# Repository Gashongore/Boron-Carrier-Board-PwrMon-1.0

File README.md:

# Boron-Carrier-Board-PwrWon-1.0
1. modified Particle Boron-Carrier-Board for Power Monitoring
2. It is using all analog pins

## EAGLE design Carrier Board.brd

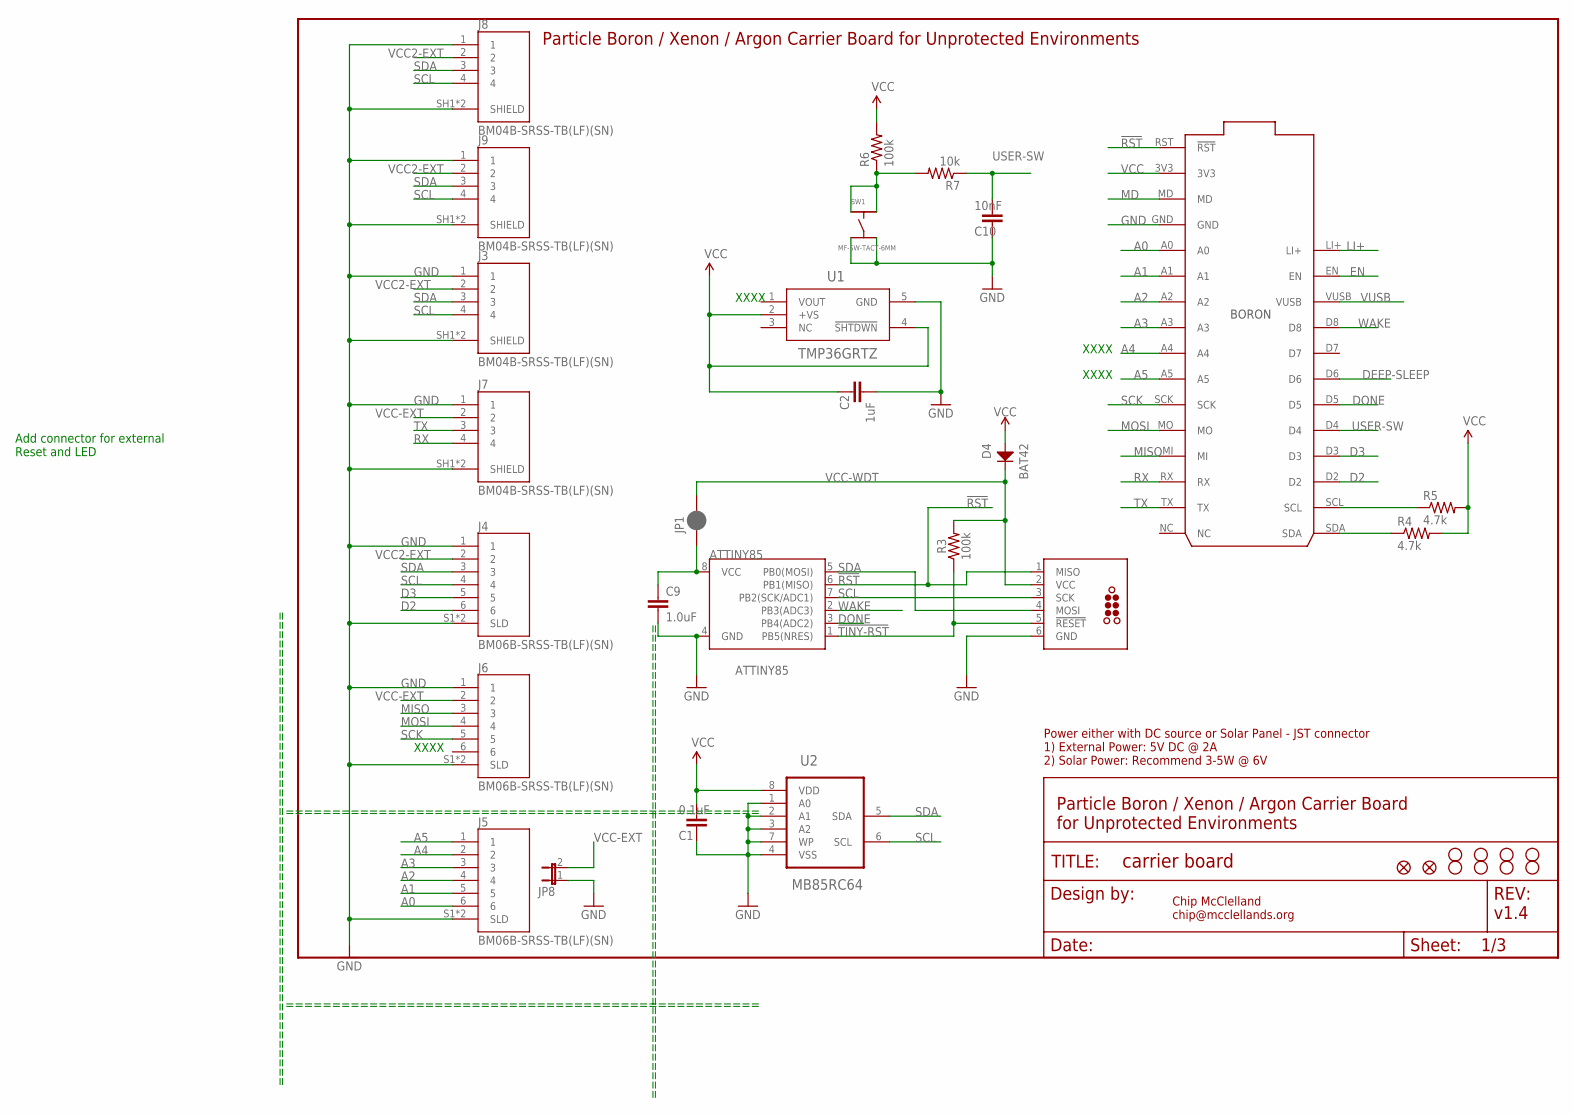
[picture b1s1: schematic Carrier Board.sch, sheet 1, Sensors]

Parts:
ATTINY85: ATTINY85; SO08-EIAJ; MPN ATTINY85-20SUR
C1: 0.1uF; 0805@1; MPN MF-CAP-0805-0.1uF
C2: 1uF; 0805@1; MPN MF-CAP-0805-1uF
C9: 1.0uF; 0805; MPN MF-CAP-0805-0.1uF
C10: 10nF; 0805@1; MPN 08051C103K4T2A
D4: BAT42; SOD-123
FD1, FD2: FIDUCIALUFIDUCIAL; FIDUCIAL-MICRO
FRAME1: FRAME-LETTER; CREATIVE_COMMONS
H1, H2, H3, H4: STAND-OFF-M2.5
ICSP: TCP2030-MCP-NL; TC2030-MCP-NL
J3, J7, J8, J9: BM04B-SRSS-TB(LF)(SN); CONN_BM04B-SRSS-TBT(LF)(SN)
J4, J5, J6: BM06B-SRSS-TB(LF)(SN); JST_BM06B-SRSS-TB(LF)(SN)
JP1: JUMPER-SMT_2_NC_PASTE_SILK; SMT-JUMPER_2_NC_PASTE_SILK
JP3, JP4, JP5, JP6: STAND-OFF
JP8: JP1E; JP1
P1: Particle Boron / Xenon / Argon; PARTICLE-DEVICES_BORON
R3, R6: 100k; 0805; MPN MF-RES-0805-100K
R4, R5: 4.7k; 0805; MPN MF-RES-0805-4.7K
R7: 10k; 0805; MPN MF-RES-0805-10K
SW1: MF-SW-TACT-6MM; TACT6MM
U1: TMP36GRTZ; RJ_5; MANUFACTURER_PART_NUMBER TMP36GRTZ-REEL7
U2: MB85RC64; SOIC127P600X175-8N; MPN MB85RC64APNF-G-JNERE1

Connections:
!RST: ATTINY85.6 (PB1(MISO)), ICSP.1 (MISO), P1.RST (!RST)
!TINY-RST: ATTINY85.1 (PB5(NRES)), ICSP.5 (!RESET), R3.1
A0: J5.6, P1.A0
A1: J5.5, P1.A1
A2: J5.4, P1.A2
A3: J5.3, P1.A3
A4: J5.2, P1.A4
A5: J5.1, P1.A5
D2: J4.6, P1.D2; also elsewhere on the board
D3: J4.5, P1.D3; also elsewhere on the board
DEEP-SLEEP: P1.D6
DONE: ATTINY85.3 (PB4(ADC2)), P1.D5
EN: P1.EN; also elsewhere on the board
GND: ATTINY85.4 (GND), C1.2, C2.2, C9.2, C10.2, ICSP.6 (GND), J3.1, J3.SH1 (SHIELD), J3.SH2 (SHIELD), J4.1, J4.S1 (SLD), J4.S2 (SLD), J5.S1 (SLD), J5.S2 (SLD), J6.1, J6.S1 (SLD), J6.S2 (SLD), J7.1, J7.SH1 (SHIELD), J7.SH2 (SHIELD), J8.1, J8.SH1 (SHIELD), J8.SH2 (SHIELD), J9.1, J9.SH1 (SHIELD), J9.SH2 (SHIELD), JP8.1, P1.GND, SW1.P$3, SW1.P$4, U1.5 (GND), U2.1 (A0), U2.2 (A1), U2.3 (A2), U2.4 (VSS), U2.7 (WP); also elsewhere on the board
LI+: P1.LI+; also elsewhere on the board
MD: P1.MD
MISO: J6.3, P1.MI
MOSI: J6.4, P1.MO
unnamed: R6.1, R7.2, SW1.P$1, SW1.P$2
unnamed: ATTINY85.8 (VCC), C9.1, JP1.1
RX: J7.4, P1.RX
SCK: J6.5, P1.SCK
SCL: ATTINY85.7 (PB2(SCK/ADC1)), ICSP.3 (SCK), J3.4, J4.4, J8.4, J9.4, P1.SCL, R5.1, U2.6 (SCL); also elsewhere on the board
SDA: ATTINY85.5 (PB0(MOSI)), ICSP.4 (MOSI), J3.3, J4.3, J8.3, J9.3, P1.SDA, R4.1, U2.5 (SDA); also elsewhere on the board
TX: J7.3, P1.TX
USER-SW: C10.1, P1.D4, R7.1
VCC: C1.1, C2.1, D4.ANODE, P1.3V3, R4.2, R5.2, R6.2, U1.2 (+VS), U1.4 (!SHTDWN), U2.8 (VDD); also elsewhere on the board
VCC2-EXT: J3.2, J4.2, J8.2, J9.2; also elsewhere on the board
VCC-EXT: J6.2, J7.2, JP8.2; also elsewhere on the board
VCC-WDT: D4.CATHODE, ICSP.2 (VCC), JP1.2, R3.2
VUSB: P1.VUSB; also elsewhere on the board
WAKE: ATTINY85.2 (PB3(ADC3)), P1.D8

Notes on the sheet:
Chip McClelland chip@mcclellands.org
v1.4
Power either with DC source or Solar Panel - JST connector 1) External Power: 5V DC @ 2A 2) Solar Power: Recommend 3-5W @ 6V
Particle Boron / Xenon / Argon Carrier Board for Unprotected Environments
Particle Boron / Xenon / Argon Carrier Board for Unprotected Environments
Add connector for external Reset and LED
===================================================
XXXX

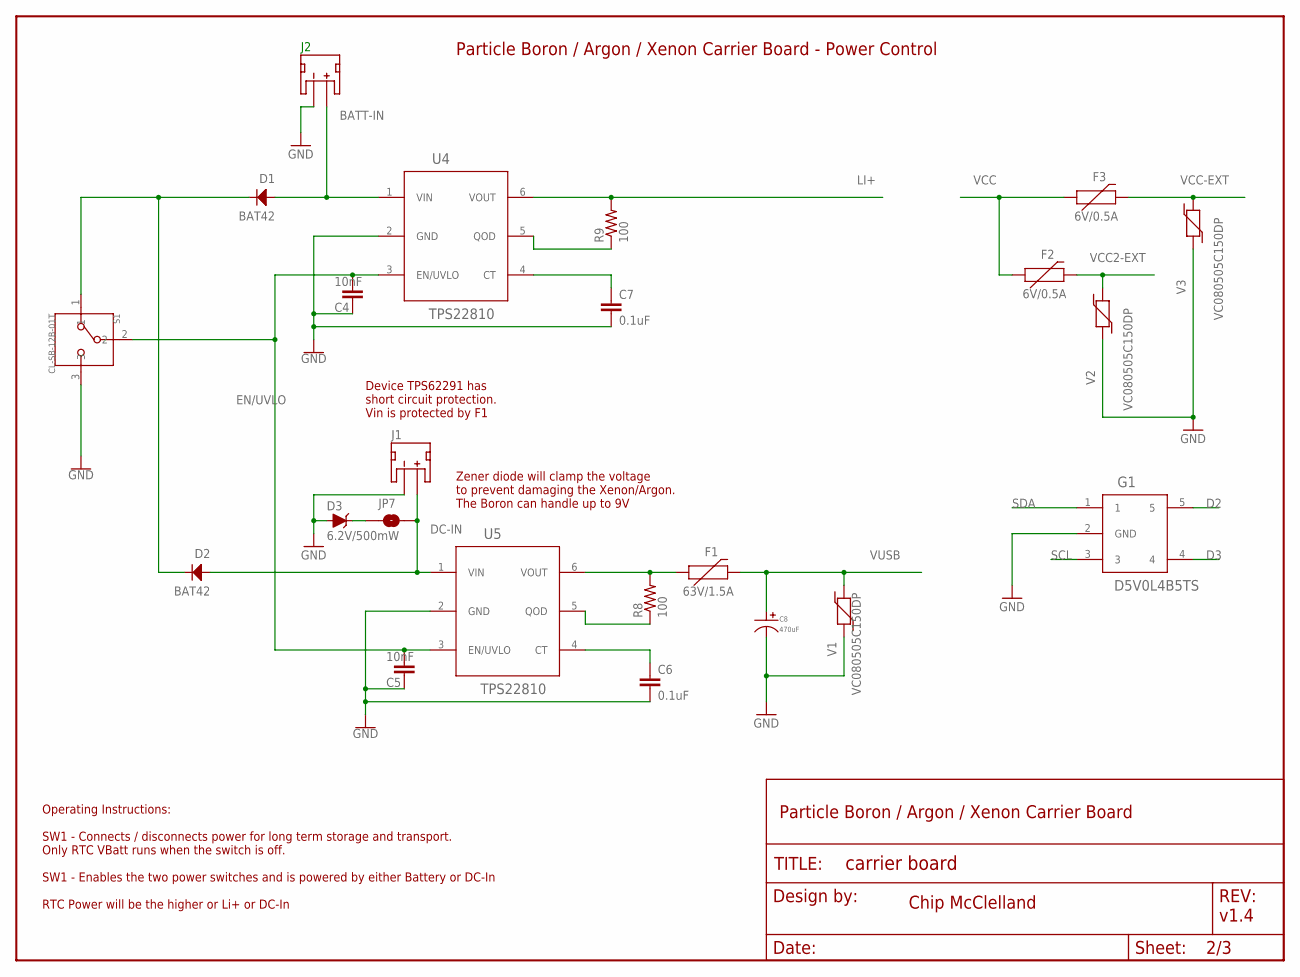
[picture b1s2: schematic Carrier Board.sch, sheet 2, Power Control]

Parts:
C4, C5: 10nF; 0805@1; MPN 08051C103K4T2A
C6, C7: 0.1uF; 0805@1; MPN MF-CAP-0805-0.1uF
C8: 470uF; CP10MM; MPN MF-CAP-10MM-470uF
D1, D2: BAT42; SOD-123
D3: 6.2V/500mW; PANASONIC_SMINI2-F5-B; MPN TDZ6V2J,115
F1: 63V/1.5A; 1206; MPN 046801.5NR
F2, F3: 6V/0.5A; 1206; MPN 0466.500NR
FRAME2: FRAME-LETTER; CREATIVE_COMMONS
G1: D5V0L4B5TS; SOT-23-5; MPN D5V0L4B5TS-7
J1, J2: S2B-PH-SM4-TB(LF)(SN); JST-2-SMD
JP7: JUMPER-SMT_2_NO_SILK; SMT-JUMPER_2_NO_SILK
R8, R9: 100; 0805; MPN MF-RES-0805-100
S1: CL-SB-12B-01T; CL-SB-12B
U4, U5: TPS22810; SOT-23-6; MPN TPS22810DBVT
V1, V2, V3: VC080505C150DP; 0805; MPN VC080505C150DP

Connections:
BATT-IN: D1.ANODE, J2.2 (+), U4.1 (VIN); also elsewhere on the board
D2: G1.5; also elsewhere on the board
D3: G1.4; also elsewhere on the board
DC-IN: D2.ANODE, J1.2 (+), JP7.1, U5.1 (VIN)
EN/UVLO: C4.1, C5.1, S1.2, U4.3 (EN/UVLO), U5.3 (EN/UVLO)
GND: C4.2, C5.2, C6.2, C7.2, C8.P$2, D3.A, G1.2 (GND), J1.1 (-), J2.1 (-), S1.3, U4.2 (GND), U5.2 (GND), V1.1, V2.1, V3.1; also elsewhere on the board
LI+: R9.2, U4.6 (VOUT); also elsewhere on the board
unnamed: D3.C, JP7.2
unnamed: C6.1, U5.4 (CT)
unnamed: R8.1, U5.5 (QOD)
unnamed: F1.1, R8.2, U5.6 (VOUT)
unnamed: D1.CATHODE, D2.CATHODE, S1.1
unnamed: C7.1, U4.4 (CT)
unnamed: R9.1, U4.5 (QOD)
SCL: G1.3; also elsewhere on the board
SDA: G1.1; also elsewhere on the board
VCC: F2.1, F3.1; also elsewhere on the board
VCC2-EXT: F2.2, V2.2; also elsewhere on the board
VCC-EXT: F3.2, V3.2; also elsewhere on the board
VUSB: C8.P$1, F1.2, V1.2; also elsewhere on the board

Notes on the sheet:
Particle Boron / Argon / Xenon Carrier Board - Power Control
Chip McClelland
v1.4
Device TPS62291 has short circuit protection. Vin is protected by F1
Particle Boron / Argon / Xenon Carrier Board
Operating Instructions: SW1 - Connects / disconnects power for long term storage and transport. Only RTC VBatt runs when the switch is off. SW1 - Enables the two power switches and is powered by either Battery or DC-In RTC Power will be the higher or Li+ or DC-In
Zener diode will clamp the voltage to prevent damaging the Xenon/Argon. The Boron can handle up to 9V

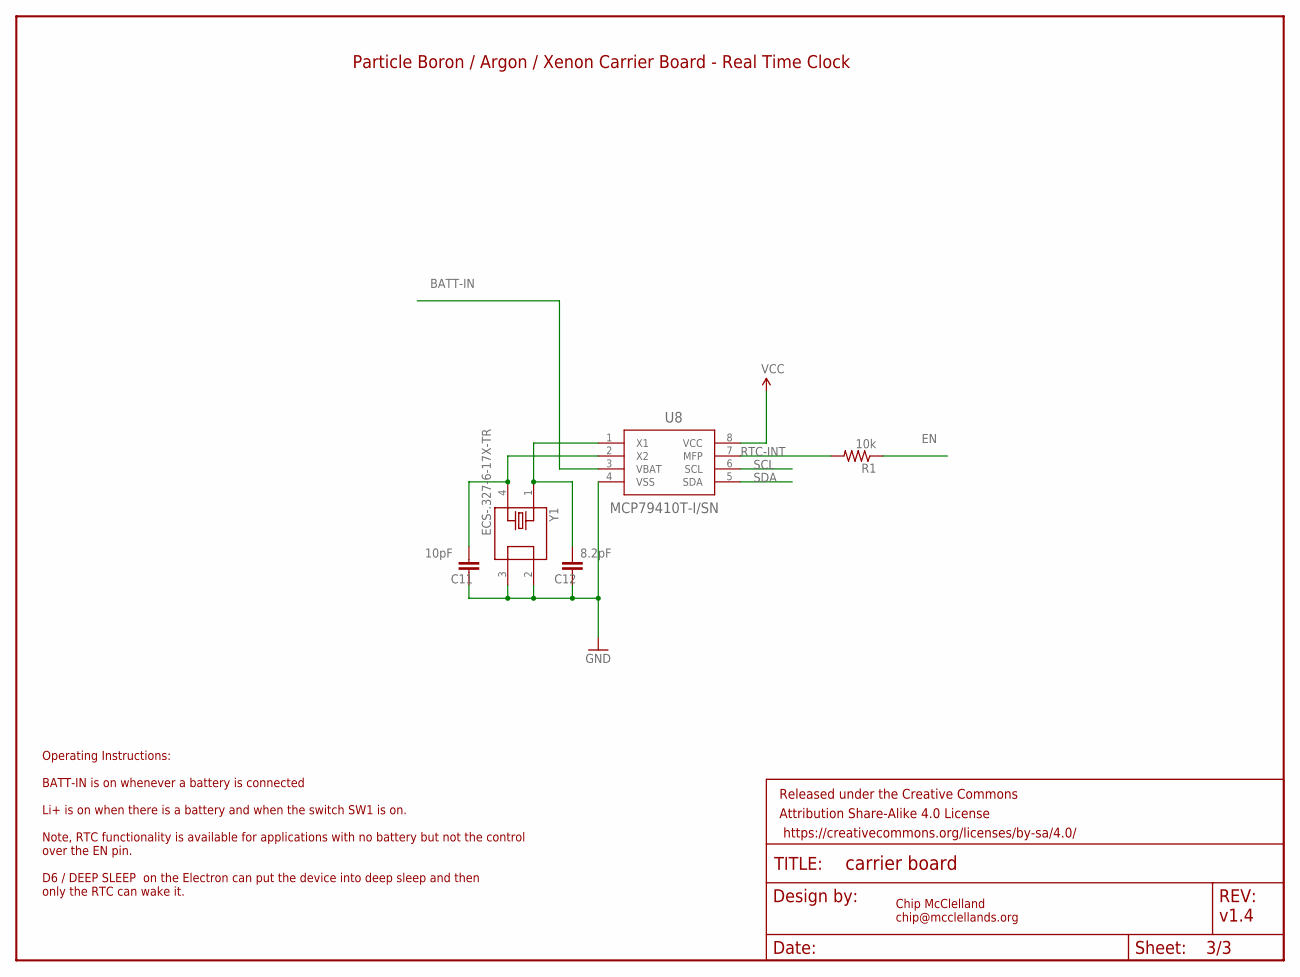
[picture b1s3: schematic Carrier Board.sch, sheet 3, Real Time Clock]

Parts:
C11: 10pF; 0805@1; MPN C0805C100JDGACTU‎
C12: 8.2pF; 0805@1; MPN C0805C829D5GACTU‎
FRAME3: FRAME-LETTER; CREATIVE_COMMONS
R1: 10k; 0805; MPN MF-RES-0805-10K
U8: MCP79410T-I/SN; SOIC8-N_MC
Y1: ECS-.327-6-17X-TR; XTAL_ECS-.327-6-17X-TR

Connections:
BATT-IN: U8.3 (VBAT); also elsewhere on the board
EN: R1.1; also elsewhere on the board
GND: C11.2, C12.2, U8.4 (VSS), Y1.2, Y1.3; also elsewhere on the board
unnamed: C12.1, U8.1 (X1), Y1.1
unnamed: C11.1, U8.2 (X2), Y1.4
RTC-INT: R1.2, U8.7 (MFP)
SCL: U8.6 (SCL); also elsewhere on the board
SDA: U8.5 (SDA); also elsewhere on the board
VCC: U8.8 (VCC); also elsewhere on the board

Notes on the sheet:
Operating Instructions: BATT-IN is on whenever a battery is connected Li+ is on when there is a battery and when the switch SW1 is on. Note, RTC functionality is available for applications with no battery but not the control over the EN pin. D6 / DEEP SLEEP on the Electron can put the device into d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
Particle Boron / Argon / Xenon Carrier Board - Real Time Clock
Chip McClelland chip@mcclellands.org
v1.4

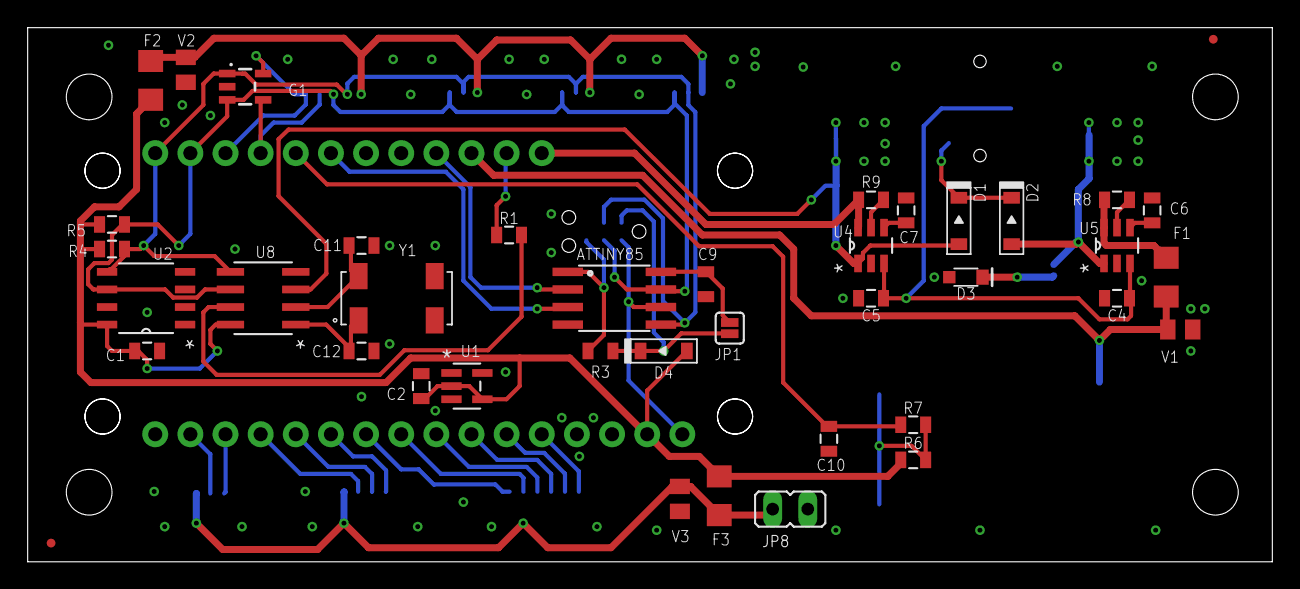
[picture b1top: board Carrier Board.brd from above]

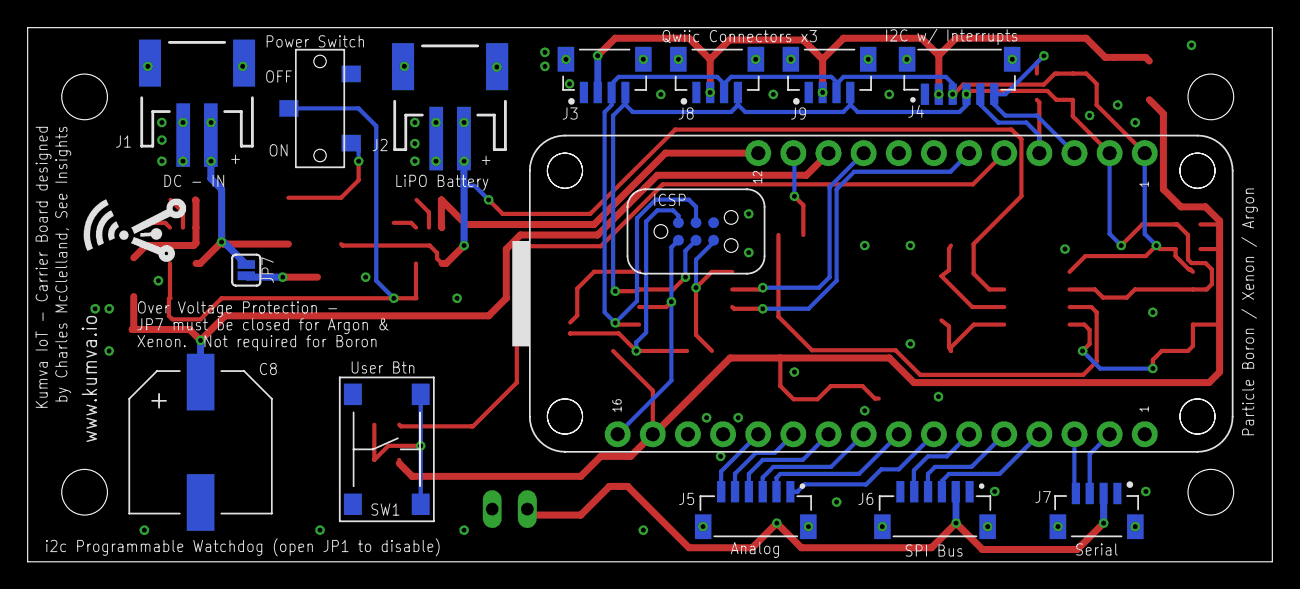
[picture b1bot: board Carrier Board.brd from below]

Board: 2 copper layers, 90.0 x 38.6 mm, 66 parts (15 on the bottom side), 43 nets.

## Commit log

2020-11-02 Particle Boron Carrier board 1.4 modified to use all 6 Analog Pins
2020-11-08 -Added logo -Production ready
2020-11-21 Final_Production_Ready

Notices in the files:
parts and their libraries:
SparkFun-Aesthetics: Licensing: Creative Commons ShareAlike 4.0 International - https://creativecommons.org/licenses/by-sa/4.0
SparkFun-Aesthetics: Released under the Creative Commons Attribution Share-Alike 4.0 License
SparkFun-Aesthetics: https://creativecommons.org/licenses/by-sa/4.0
